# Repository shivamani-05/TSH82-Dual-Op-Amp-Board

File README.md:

# TSH82-Dual-Op-Amp-Board
This PCB is a breakout for the TSH82, a high-speed dual operational amplifier. It's designed for video and high-frequency signal processing applications. The board provides easy access to both amplifier channels, with dedicated inputs, outputs, and power connections, making it ideal for prototyping and integration into larger systems

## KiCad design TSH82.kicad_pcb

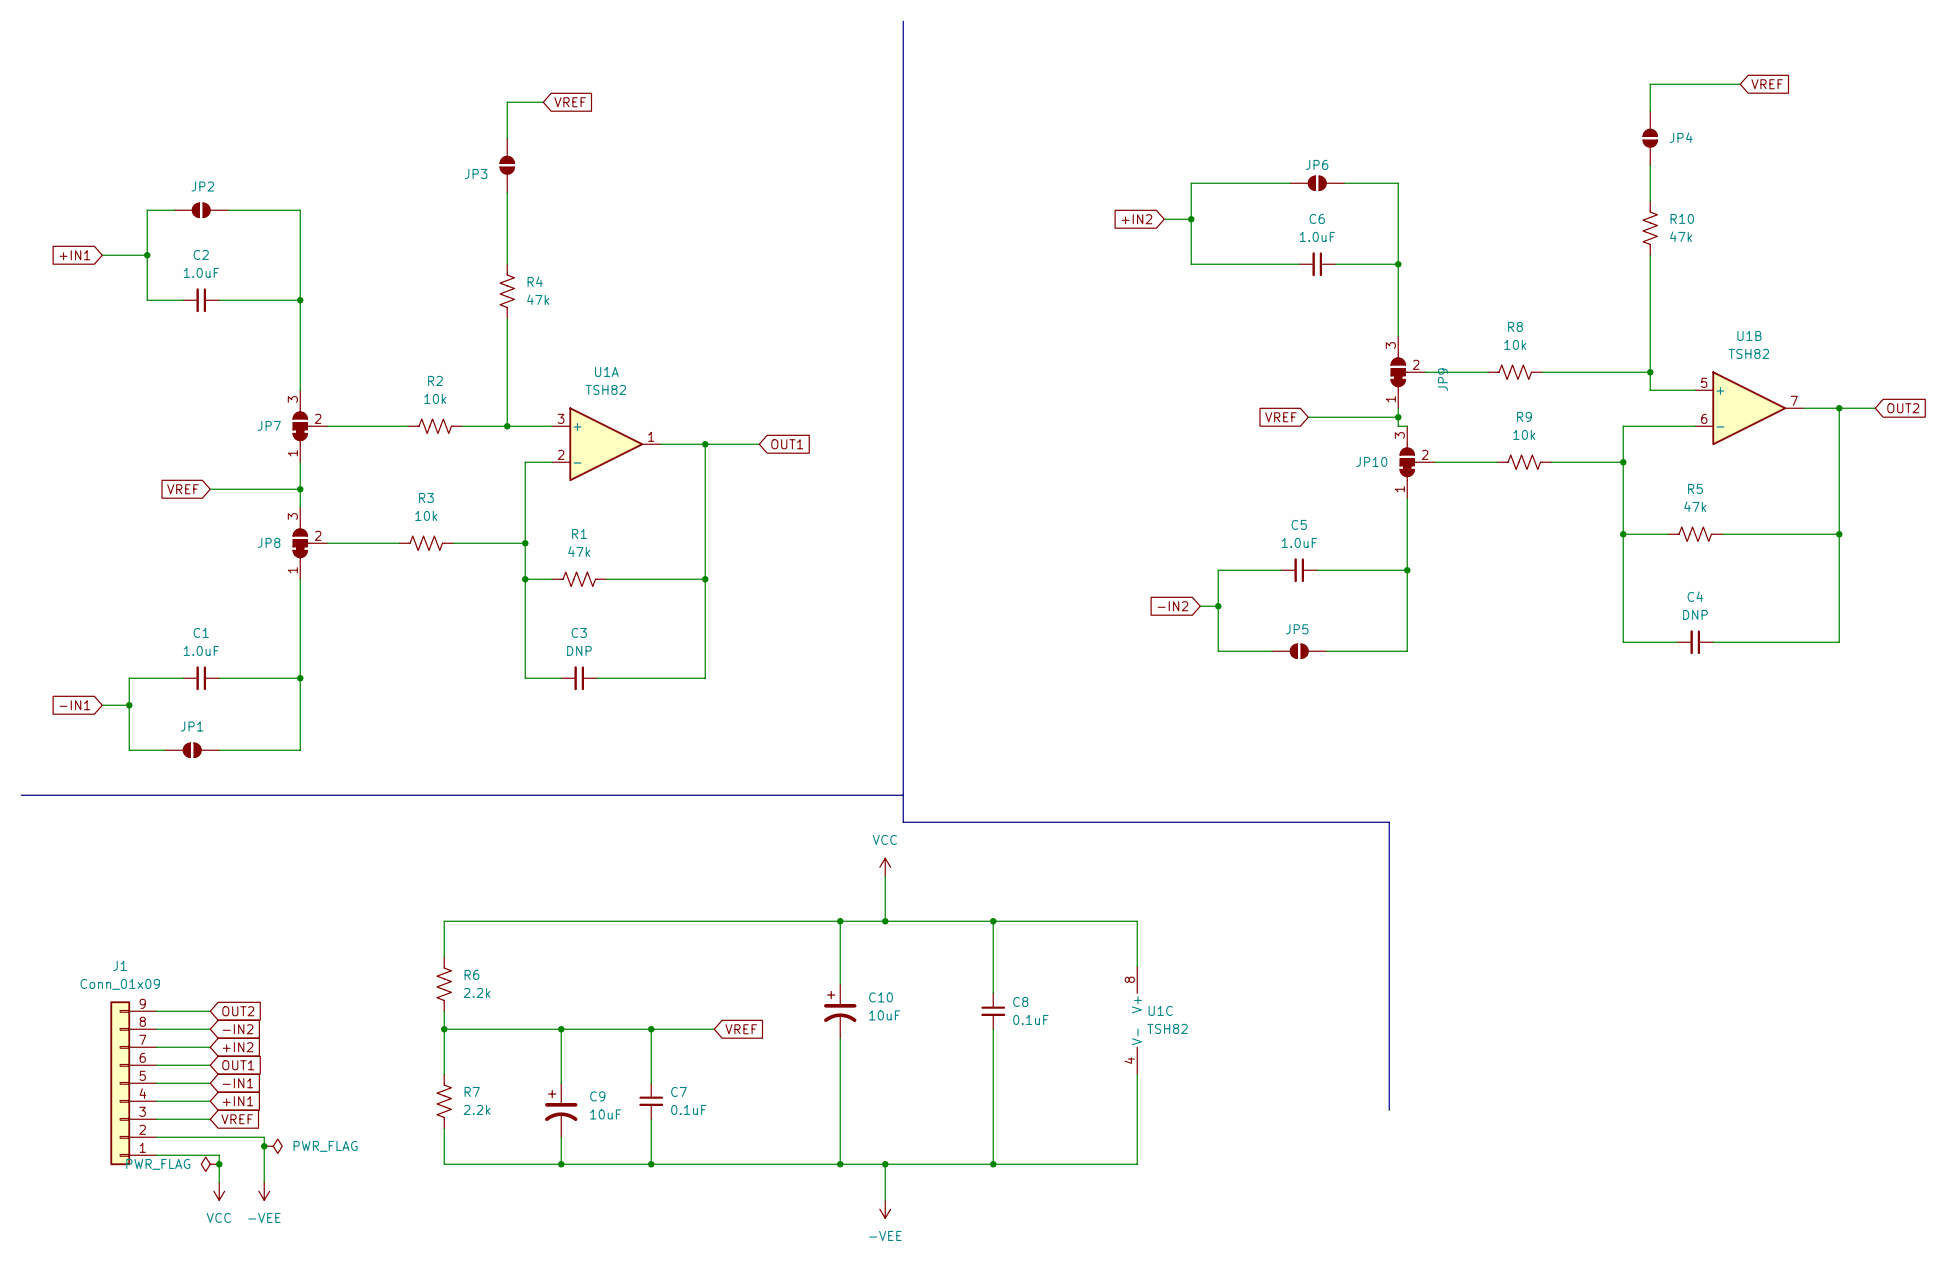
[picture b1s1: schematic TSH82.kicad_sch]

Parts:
C1, C2, C5, C6: 1.0uF; C_0603_1608Metric
C3, C4: DNP; C_0603_1608Metric
C7, C8: 0.1uF; C_0603_1608Metric
C9, C10: 10uF; C_0603_1608Metric
J1: Conn_01x09; Hirose_DF13-09P-1.25DSA_1x09_P1.25mm_Vertical
JP1, JP2, JP3, JP4, JP5, JP6: SolderJumper_2_Open; SolderJumper-2_P1.3mm_Open_Pad1.0x1.5mm
JP7, JP8, JP9, JP10: SolderJumper_3_Bridged12; SolderJumper-3_P1.3mm_Bridged12_Pad1.0x1.5mm
R1, R4, R5, R10: 47k; R_0603_1608Metric
R2, R3, R8, R9: 10k; R_0603_1608Metric
R6, R7: 2.2k; R_0603_1608Metric
U1: TSH82; SOIC-8-1EP_3.9x4.9mm_P1.27mm_EP2.29x3mm

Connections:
+IN1: C2.2, J1.4, JP2.1 (A)
+IN2: C6.2, J1.7, JP6.1 (A)
-IN1: C1.2, J1.5, JP1.1 (A)
-IN2: C5.2, J1.8, JP5.1 (A)
-VEE: C7.2, C8.2, C9.2, C10.2, J1.2, R7.2, U1.4 (V-)
unnamed: C1.1, JP1.2 (B), JP8.1 (A)
unnamed: C2.1, JP2.2 (B), JP7.3 (B)
unnamed: JP3.1 (A), R4.1
unnamed: JP4.2 (B), R10.2
unnamed: C6.1, JP6.2 (B), JP9.3 (B)
unnamed: JP7.2 (C), R2.2
unnamed: JP8.2 (C), R3.2
unnamed: JP9.2 (C), R8.2
unnamed: C5.1, JP5.2 (B), JP10.1 (A)
unnamed: JP10.2 (C), R9.2
unnamed: R2.1, R4.2, U1.3 (+)
unnamed: C3.2, R1.2, R3.1, U1.2 (-)
unnamed: R8.1, R10.1, U1.5 (+)
unnamed: C4.2, R5.2, R9.1, U1.6 (-)
OUT1: C3.1, J1.6, R1.1, U1.1
OUT2: C4.1, J1.9, R5.1, U1.7
VCC: C8.1, C10.1, J1.1, R6.1, U1.8 (V+)
VREF: C7.1, C9.1, J1.3, JP3.2 (B), JP4.1 (A), JP7.1 (A), JP8.3 (B), JP9.1 (A), JP10.3 (B), R6.2, R7.1

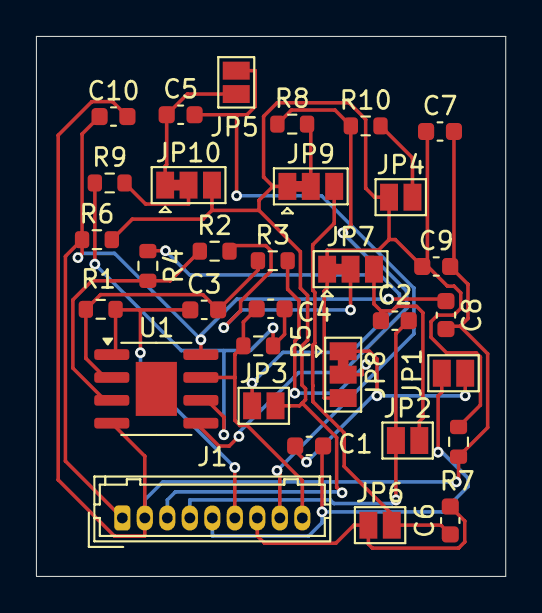
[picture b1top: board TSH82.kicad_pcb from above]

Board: 2 copper layers, 26.1 x 30.0 mm, 32 parts (0 on the bottom side), 23 nets.

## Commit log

2025-09-14 Add files via upload
    This PCB is a breakout for the TSH82, a high-speed dual operational amplifier. It's designed for video and high-frequency signal processing applications. The board provides easy access to both amplif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
